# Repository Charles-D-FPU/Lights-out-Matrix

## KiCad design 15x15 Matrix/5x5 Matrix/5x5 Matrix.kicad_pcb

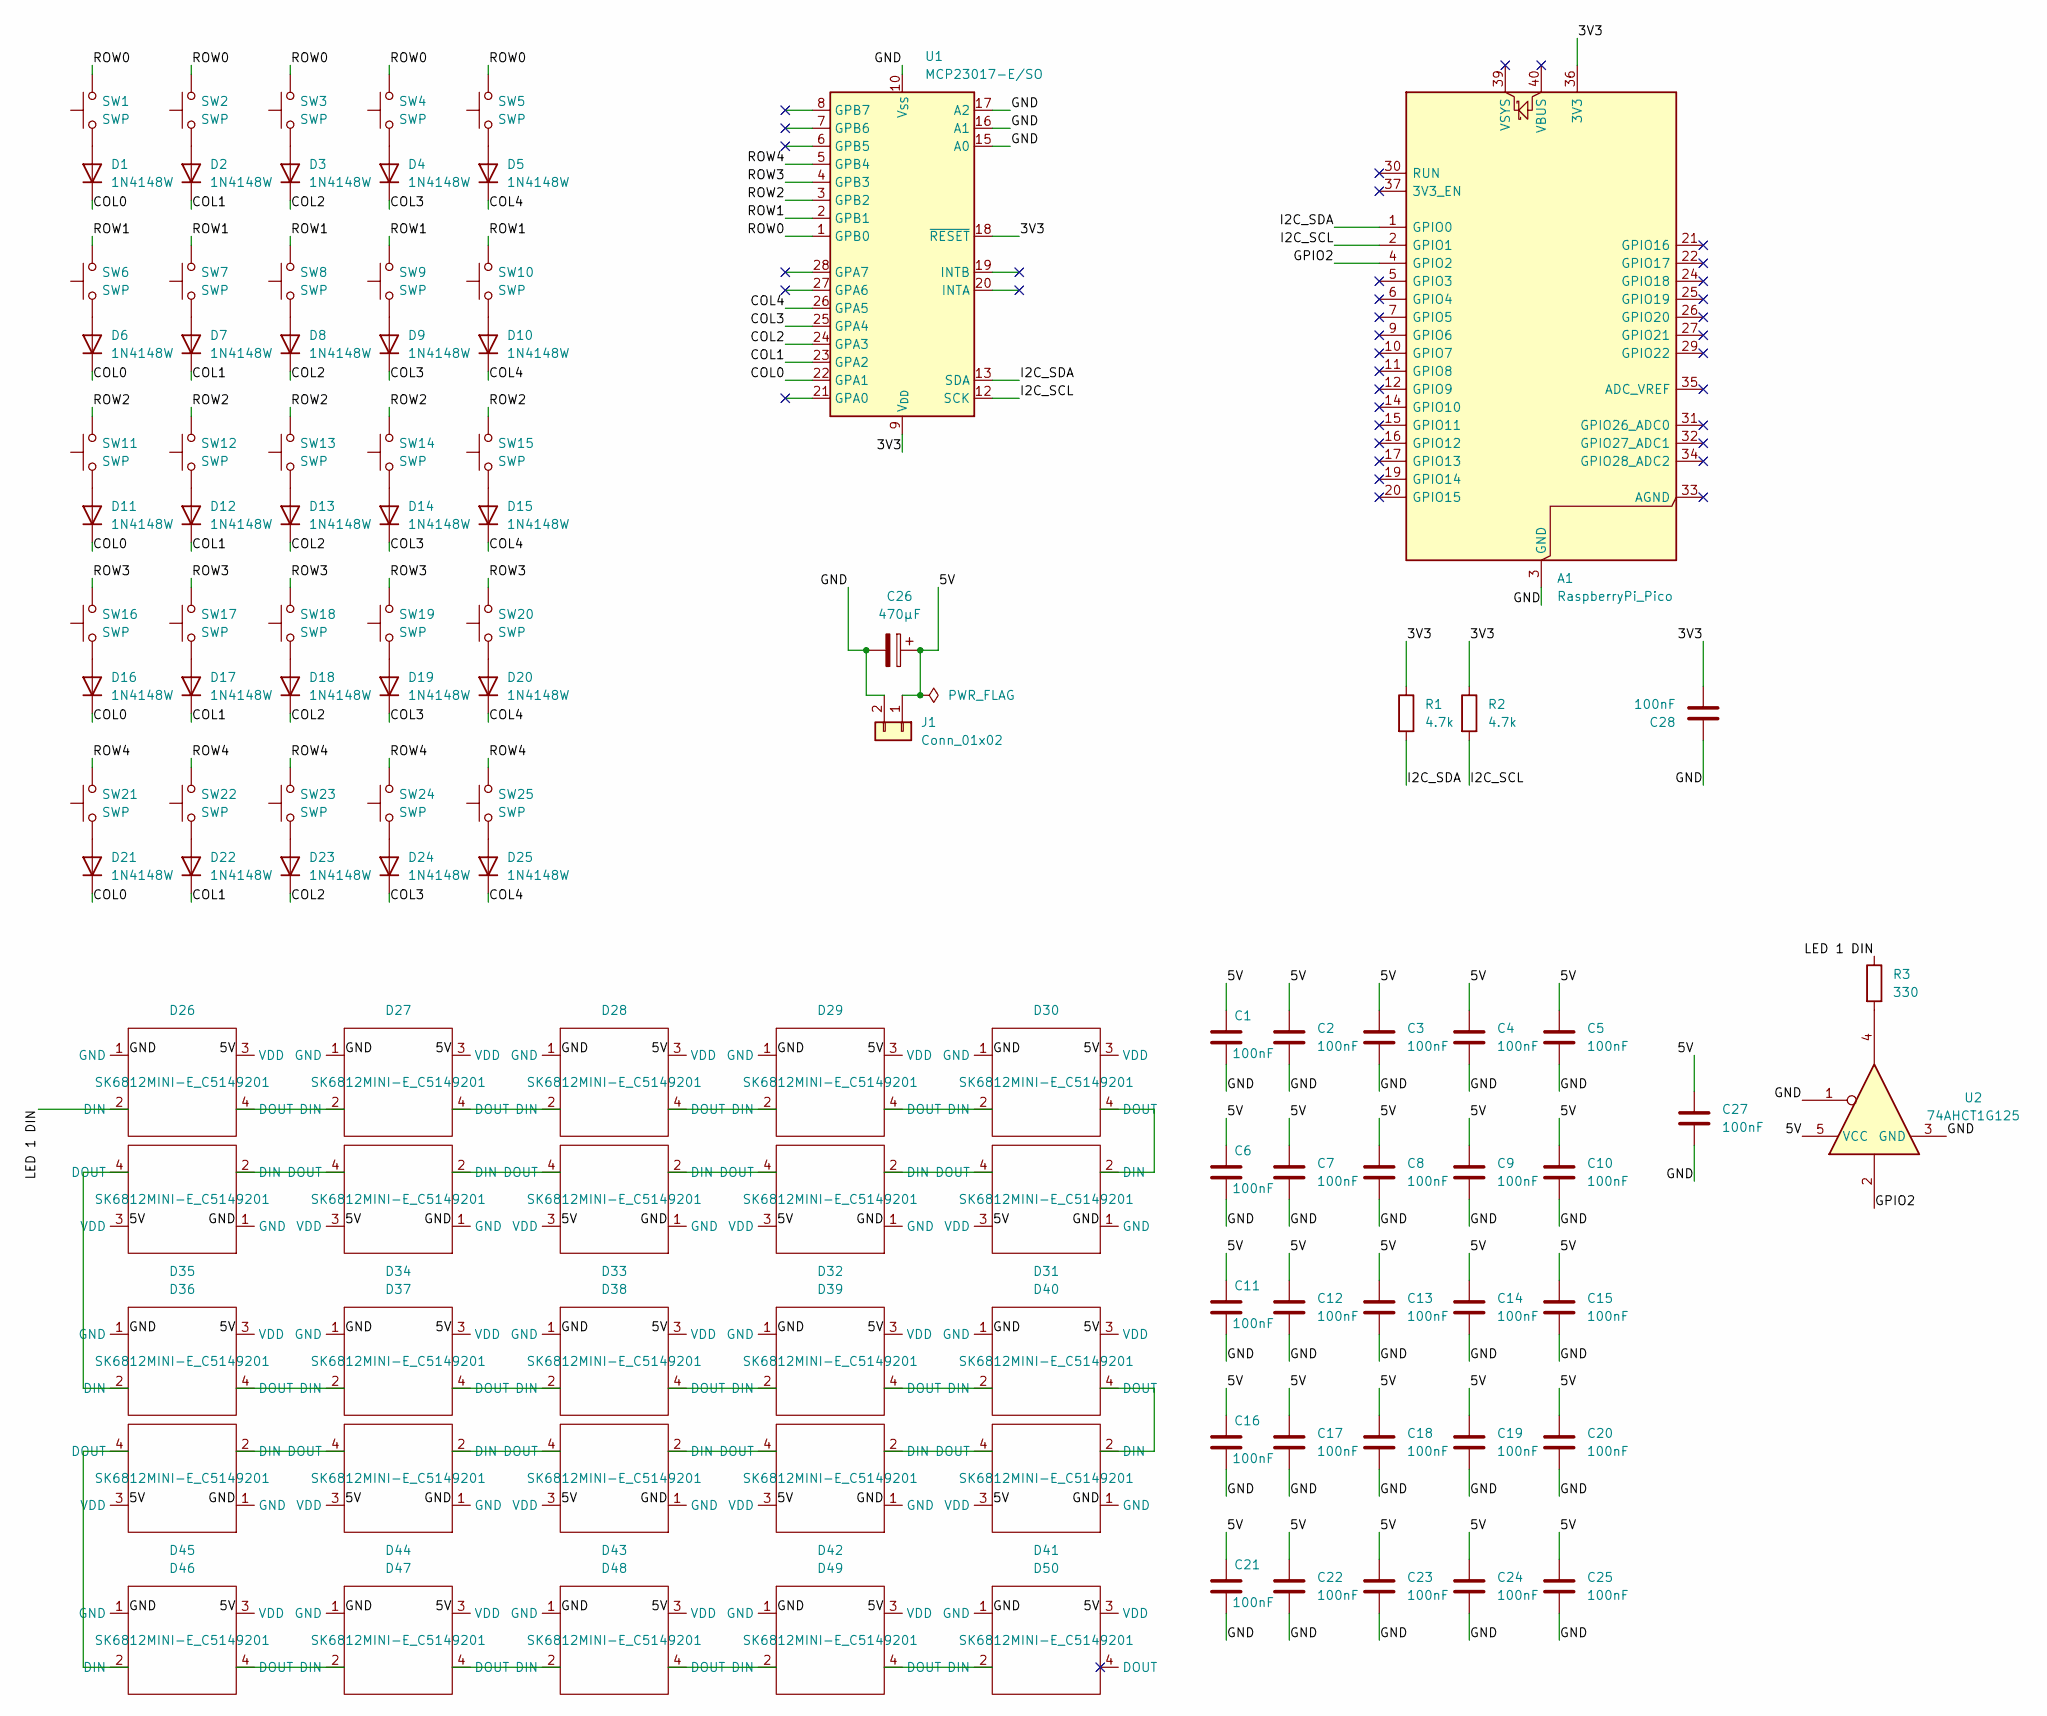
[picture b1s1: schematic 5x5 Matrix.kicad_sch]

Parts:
A1: RaspberryPi_Pico; RaspberryPi_Pico_Common_THT
C1, C2, C3, C4, C5, C6, C7, C8, C9, C10, C11, C12, C13, C14, C15, C16, C17, C18, C19, C20, C21, C22, C23, C24, C25, C27, C28: 100nF; C14663_C0603; LCSC Part # C14663
C26: 470µF; CP_Radial_D6.3mm_P2.50mm; LCSC Part # C49304896
D1, D2, D3, D4, D5, D6, D7, D8, D9, D10, D11, D12, D13, D14, D15, D16, D17, D18, D19, D20, D21, D22, D23, D24, D25: 1N4148W; C2828417_SOD-123_L2_7-W1_6-LS3_7-RD; LCSC Part # C2828417
D26, D27, D28, D29, D30, D31, D32, D33, D34, D35, D36, D37, D38, D39, D40, D41, D42, D43, D44, D45, D46, D47, D48, D49, D50: SK6812MINI-E_C5149201; LED_SK6812MINI-E_3.2x2.8mm_P1.5mm_ReverseMount; LCSC Part # C5149201
J1: Conn_01x02; C474906_CONN-TH_P5_08_KF127-5_08-2P; LCSC Part # C474906
R1, R2: 4.7k; C23162_R0603; LCSC Part # C23162
R3: 330; C105881_R0603; LCSC Part # C105881
SW1, SW2, SW3, SW4, SW5, SW6, SW7, SW8, SW9, SW10, SW11, SW12, SW13, SW14, SW15, SW16, SW17, SW18, SW19, SW20, SW21, SW22, SW23, SW24, SW25: SWP; SW_Cherry_MX_1.00u_PCB
U1: MCP23017-E/SO; C47023_SOIC-28_L18_0-W7_5-P1_27-LS10_3-BL; LCSC Part # C47023
U2: 74AHCT1G125; C7484_SOT-23-5_L3_0-W1_7-P0_95-LS2_8-BR; LCSC Part # C7484

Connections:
/3V3: A1.36 (3V3), C28.2, R1.1, R2.1, U1.9 (V_{DD}), U1.18 (~RESET)
/5V: C1.1, C2.1, C3.1, C4.1, C5.1, C6.1, C7.1, C8.1, C9.1, C10.1, C11.1, C12.1, C13.1, C14.1, C15.1, C16.1, C17.1, C18.1, C19.1, C20.1, C21.1, C22.1, C23.1, C24.1, C25.1, C26.1, C27.2, D26.3 (VDD), D27.3 (VDD), D28.3 (VDD), D29.3 (VDD), D30.3 (VDD), D31.3 (VDD), D32.3 (VDD), D33.3 (VDD), D34.3 (VDD), D35.3 (VDD), D36.3 (VDD), D37.3 (VDD), D38.3 (VDD), D39.3 (VDD), D40.3 (VDD), D41.3 (VDD), D42.3 (VDD), D43.3 (VDD), D44.3 (VDD), D45.3 (VDD), D46.3 (VDD), D47.3 (VDD), D48.3 (VDD), D49.3 (VDD), D50.3 (VDD), J1.1, U2.5 (VCC)
/COL0: D1.1 (K), D6.1 (K), D11.1 (K), D16.1 (K), D21.1 (K), U1.22 (GPA1)
/COL1: D2.1 (K), D7.1 (K), D12.1 (K), D17.1 (K), D22.1 (K), U1.23 (GPA2)
/COL2: D3.1 (K), D8.1 (K), D13.1 (K), D18.1 (K), D23.1 (K), U1.24 (GPA3)
/COL3: D4.1 (K), D9.1 (K), D14.1 (K), D19.1 (K), D24.1 (K), U1.25 (GPA4)
/COL4: D5.1 (K), D10.1 (K), D15.1 (K), D20.1 (K), D25.1 (K), U1.26 (GPA5)
/GND: A1.3 (GND), A1.8 (GND), A1.13 (GND), A1.18 (GND), A1.23 (GND), A1.28 (GND), A1.38 (GND), C1.2, C2.2, C3.2, C4.2, C5.2, C6.2, C7.2, C8.2, C9.2, C10.2, C11.2, C12.2, C13.2, C14.2, C15.2, C16.2, C17.2, C18.2, C19.2, C20.2, C21.2, C22.2, C23.2, C24.2, C25.2, C26.2, C27.1, C28.1, D26.1 (GND), D27.1 (GND), D28.1 (GND), D29.1 (GND), D30.1 (GND), D31.1 (GND), D32.1 (GND), D33.1 (GND), D34.1 (GND), D35.1 (GND), D36.1 (GND), D37.1 (GND), D38.1 (GND), D39.1 (GND), D40.1 (GND), D41.1 (GND), D42.1 (GND), D43.1 (GND), D44.1 (GND), D45.1 (GND), D46.1 (GND), D47.1 (GND), D48.1 (GND), D49.1 (GND), D50.1 (GND), J1.2, U1.10 (V_{SS}), U1.15 (A0), U1.16 (A1), U1.17 (A2), U2.1, U2.3 (GND)
/GPIO2: A1.4 (GPIO2), U2.2
/I2C_SCL: A1.2 (GPIO1), R2.2, U1.12 (SCK)
/I2C_SDA: A1.1 (GPIO0), R1.2, U1.13 (SDA)
/LED 1 DIN: D26.2 (DIN), R3.1
/ROW0: SW1.2, SW2.2, SW3.2, SW4.2, SW5.2, U1.1 (GPB0)
/ROW1: SW6.2, SW7.2, SW8.2, SW9.2, SW10.2, U1.2 (GPB1)
/ROW2: SW11.2, SW12.2, SW13.2, SW14.2, SW15.2, U1.3 (GPB2)
/ROW3: SW16.2, SW17.2, SW18.2, SW19.2, SW20.2, U1.4 (GPB3)
/ROW4: SW21.2, SW22.2, SW23.2, SW24.2, SW25.2, U1.5 (GPB4)
unnamed: D1.2 (A), SW1.1
unnamed: D2.2 (A), SW2.1
unnamed: D3.2 (A), SW3.1
unnamed: D4.2 (A), SW4.1
unnamed: D5.2 (A), SW5.1
unnamed: D6.2 (A), SW6.1
unnamed: D7.2 (A), SW7.1
unnamed: D8.2 (A), SW8.1
unnamed: D9.2 (A), SW9.1
unnamed: D10.2 (A), SW10.1
unnamed: D11.2 (A), SW11.1
unnamed: D12.2 (A), SW12.1
unnamed: D13.2 (A), SW13.1
unnamed: D14.2 (A), SW14.1
unnamed: D15.2 (A), SW15.1
unnamed: D16.2 (A), SW16.1
unnamed: D17.2 (A), SW17.1
unnamed: D18.2 (A), SW18.1
unnamed: D19.2 (A), SW19.1
unnamed: D20.2 (A), SW20.1
unnamed: D21.2 (A), SW21.1
unnamed: D22.2 (A), SW22.1
unnamed: D23.2 (A), SW23.1
unnamed: D24.2 (A), SW24.1
unnamed: D25.2 (A), SW25.1
unnamed: D26.4 (DOUT), D27.2 (DIN)
unnamed: D27.4 (DOUT), D28.2 (DIN)
unnamed: D28.4 (DOUT), D29.2 (DIN)
unnamed: D29.4 (DOUT), D30.2 (DIN)
unnamed: D30.4 (DOUT), D31.2 (DIN)
unnamed: D31.4 (DOUT), D32.2 (DIN)
unnamed: D32.4 (DOUT), D33.2 (DIN)
unnamed: D33.4 (DOUT), D34.2 (DIN)
unnamed: D34.4 (DOUT), D35.2 (DIN)
unnamed: D35.4 (DOUT), D36.2 (DIN)
unnamed: D36.4 (DOUT), D37.2 (DIN)
unnamed: D37.4 (DOUT), D38.2 (DIN)
unnamed: D38.4 (DOUT), D39.2 (DIN)
unnamed: D39.4 (DOUT), D40.2 (DIN)
unnamed: D40.4 (DOUT), D41.2 (DIN)
unnamed: D41.4 (DOUT), D42.2 (DIN)
unnamed: D42.4 (DOUT), D43.2 (DIN)
unnamed: D43.4 (DOUT), D44.2 (DIN)
unnamed: D44.4 (DOUT), D45.2 (DIN)
unnamed: D45.4 (DOUT), D46.2 (DIN)
unnamed: D46.4 (DOUT), D47.2 (DIN)
unnamed: D47.4 (DOUT), D48.2 (DIN)
unnamed: D48.4 (DOUT), D49.2 (DIN)
unnamed: D49.4 (DOUT), D50.2 (DIN)
unnamed: R3.2, U2.4

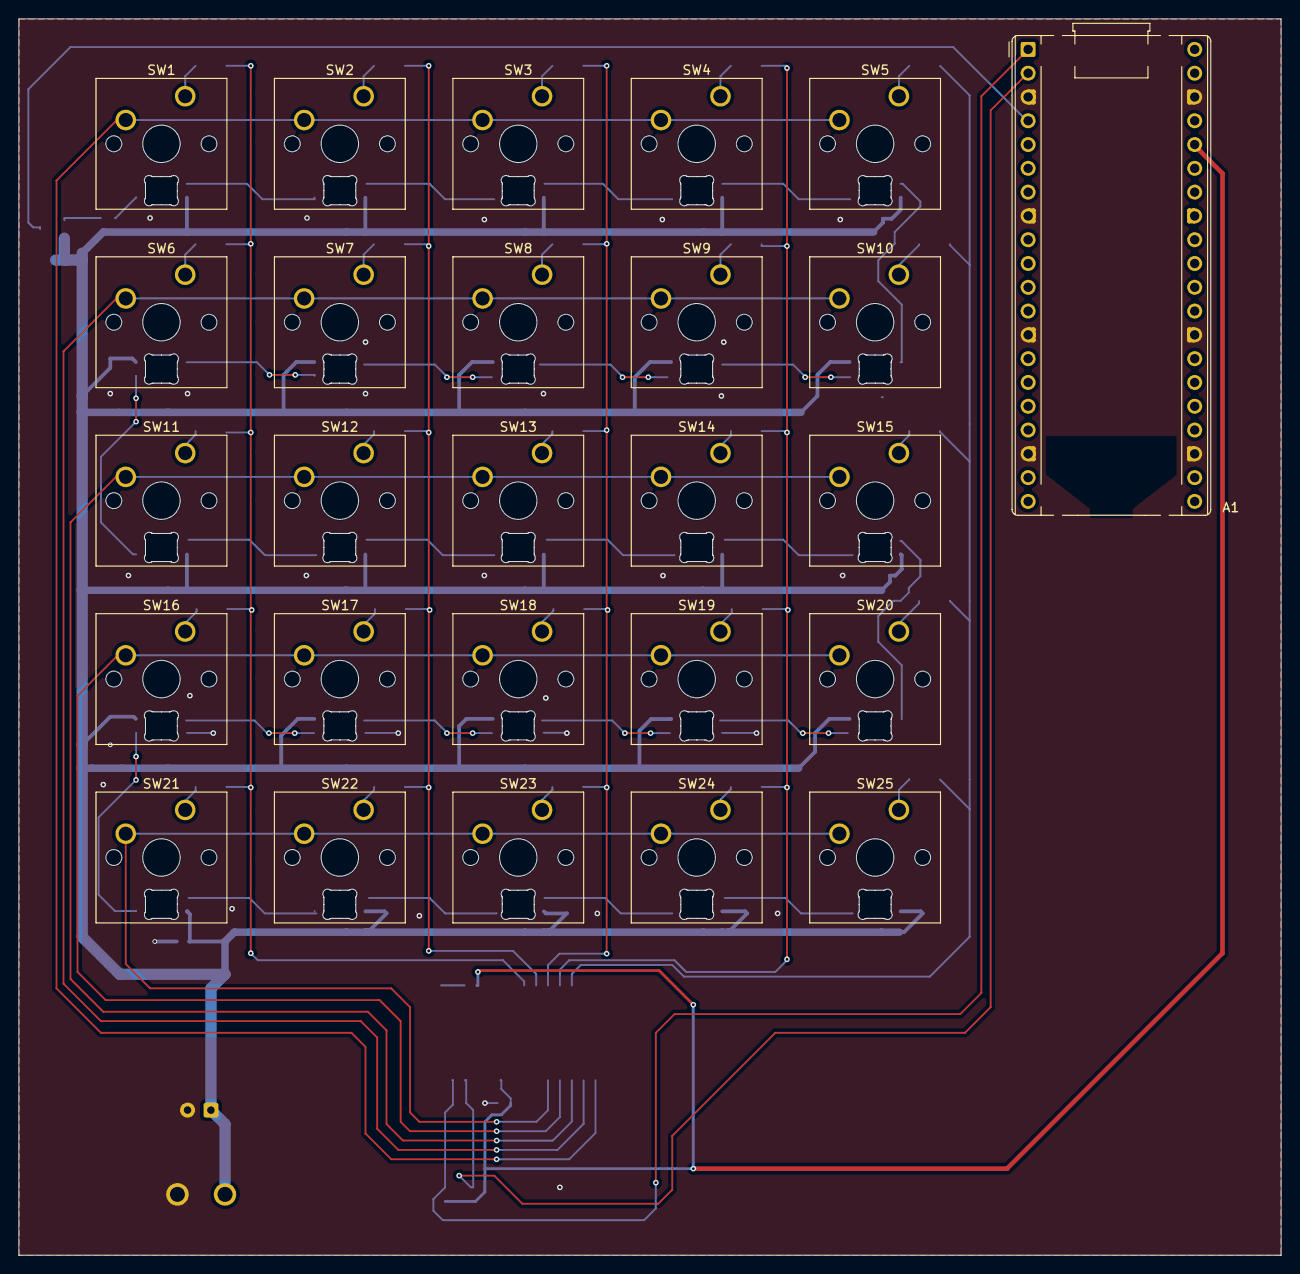
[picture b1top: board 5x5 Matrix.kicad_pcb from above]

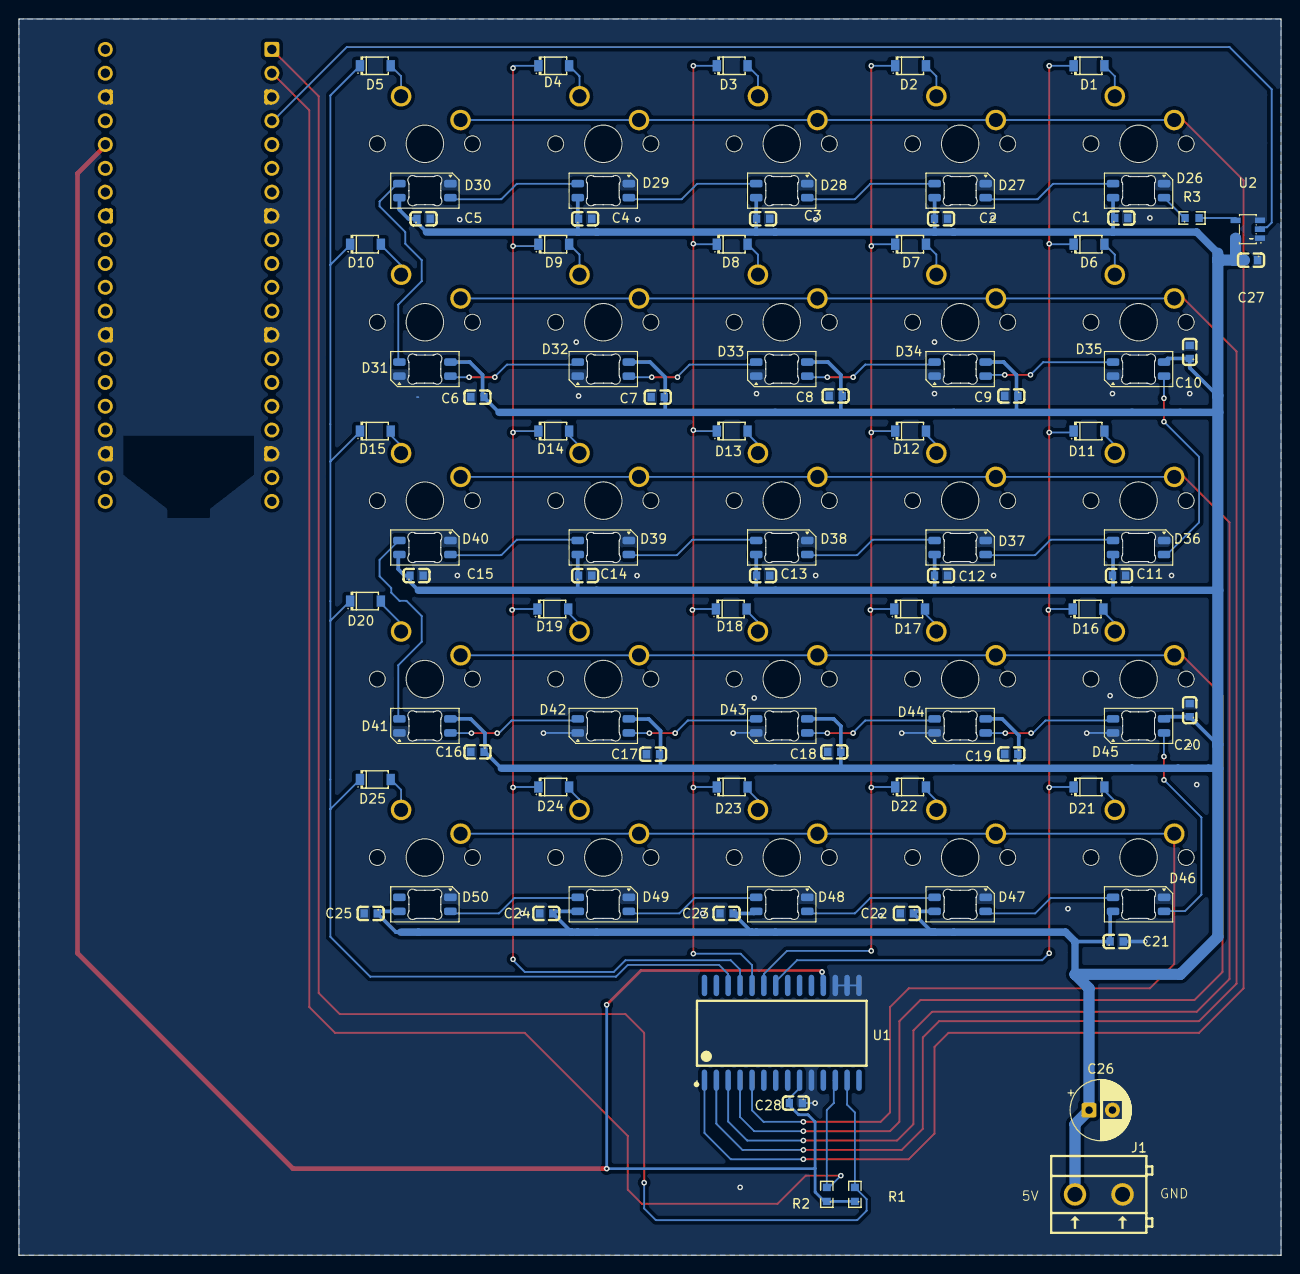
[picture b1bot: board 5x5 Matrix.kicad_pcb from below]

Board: 2 copper layers, 134.8 x 132.0 mm, 110 parts (84 on the bottom side), 67 nets.

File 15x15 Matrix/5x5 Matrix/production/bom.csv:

Designator,Footprint,Quantity,Value,LCSC Part #
"C1, C10, C11, C12, C13, C14, C15, C16, C17, C18, C19, C2, C20, C21, C22, C23, C24, C25, C27, C28, C3, C4, C5, C6, C7, C8, C9",C14663_C0603,27,100nF,C14663
C26,CP_Radial_D6.3mm_P2.50mm,1,470µF,C49304896
"D1, D10, D11, D12, D13, D14, D15, D16, D17, D18, D19, D2, D20, D21, D22, D23, D24, D25, D3, D4, D5, D6, D7, D8, D9",C2828417_SOD-123_L2_7-W1_6-LS3_7-RD,25,1N4148W,C2828417
"D26, D27, D28, D29, D30, D31, D32, D33, D34, D35, D36, D37, D38, D39, D40, D41, D42, D43, D44, D45, D46, D47, D48, D49, D50",LED_SK6812MINI-E_3.2x2.8mm_P1.5mm_ReverseMount,25,SK6812MINI-E_C5149201,C5149201
J1,C474906_CONN-TH_P5_08_KF127-5_08-2P,1,Conn_01x02,C474906
"R1, R2",C23162_R0603,2,4.7k,C23162
R3,C105881_R0603,1,330,C105881
U1,C47023_SOIC-28_L18_0-W7_5-P1_27-LS10_3-BL,1,MCP23017-E/SO,C47023
U2,C7484_SOT-23-5_L3_0-W1_7-P0_95-LS2_8-BR,1,74AHCT1G125,C7484
